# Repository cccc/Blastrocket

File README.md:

# Blastrocket - A C4 flavored Blinkenrocket

With KiCad made clone of the [https://github.com/blinkenrocket](blinkenrocket). Should be compatible with the original blinkenrocket, e.g. to use webbased [http://blinkenrocket.de/](programming tool) and the original build up manual.

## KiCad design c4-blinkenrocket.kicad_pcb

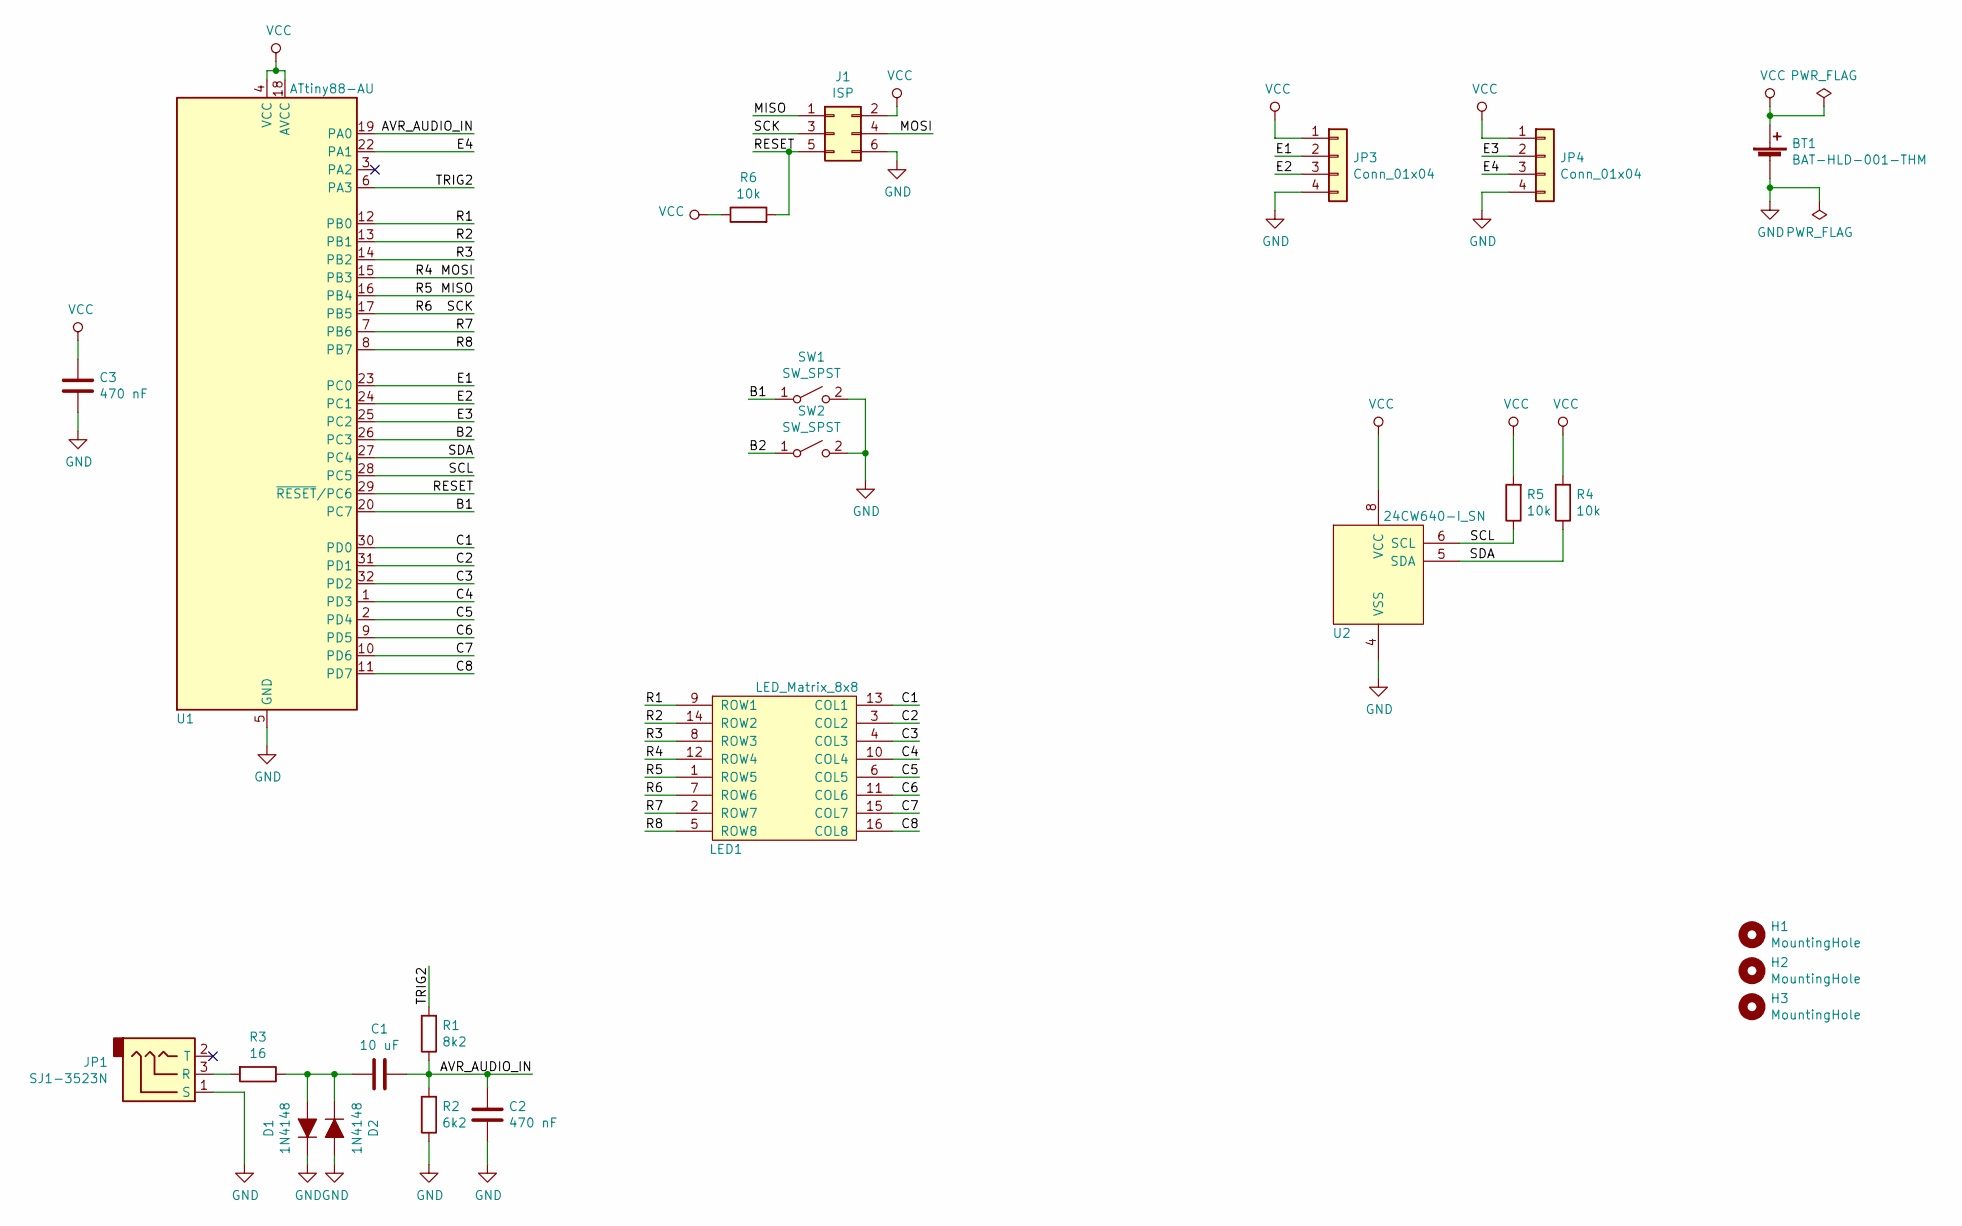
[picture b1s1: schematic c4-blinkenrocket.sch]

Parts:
BT1: BAT-HLD-001-THM; BAT_Linx_BAT-HLD-001-THM; Mfg Part Num BAT-HLD-001-THM; Digikey BAT-HLD-001-THM-ND
C1: 10 uF; C_1206_3216Metric_Pad1.42x1.75mm_HandSolder; Mfg Part Num CL31A106KAHNNNE; Digikey 1276-1075-1-ND
C2, C3: 470 nF; C_1206_3216Metric_Pad1.42x1.75mm_HandSolder; Mfg Part Num CL31B474KBHNNNE; Digikey 1276-1118-1-ND
D1, D2: 1N4148; D_SOD-123; Mfg Part Num 1N4148WQ-7-F; Digikey 1N4148WQ-7-FDICT-ND
H1, H2, H3: MountingHole; MountingHole_3.2mm_M3_Pad
J1: ISP; PinHeader_2x03_P2.54mm_Vertical
JP1: SJ1-3523N; Jack_3.5mm_CUI_SJ1-3523N_Horizontal; Mfg Part Num SJ1-3523N; Digikey CP1-3523N-ND
JP3, JP4: Conn_01x04; PinHeader_1x04_P2.54mm_Vertical
LED1: LED_Matrix_8x8; LED_KWM-30881XVB_8x8_3mm_3.2x3.2mm
R1: 8k2; R_1206_3216Metric_Pad1.42x1.75mm_HandSolder; Mfg Part Num RC1206JR-078K2L; Digikey 311-8.2KERCT-ND
R2: 6k2; R_1206_3216Metric_Pad1.42x1.75mm_HandSolder; Mfg Part Num RC1206JR-076K2L; Digikey 311-6.2KERCT-ND
R3: 16; R_1206_3216Metric_Pad1.42x1.75mm_HandSolder; Mfg Part Num RC1206FR-0716RL; Digikey 311-16.0FRCT-ND
R4, R5, R6: 10k; R_1206_3216Metric_Pad1.42x1.75mm_HandSolder; Mfg Part Num RC1206JR-0710KL; Digikey 311-10KERCT-ND
SW1, SW2: SW_SPST; SW_PUSH_6mm_H5mm; Mfg Part Num 1825910-7; Digikey 450-1804-ND
U1: ATtiny88-AU; TQFP-32_7x7mm_P0.8mm_Handsolder; Mfg Part Num ATTINY88-AU; Digikey ATTINY88-AU-ND
U2: 24CW640-I_SN; SOIC-8_4.9x3.9mm_P1.27mm_Handsolder; Mfg Part Num 24CW640-I/SN; Digikey 24CW640-I/SN-ND

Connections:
/AVR_AUDIO_IN: C1.1, C2.2, R1.1, R2.2, U1.19 (PA0)
/B1: SW1.1 (A), U1.20 (PC7)
/B2: SW2.1 (A), U1.26 (PC3)
/C1: LED1.13 (COL1), U1.30 (PD0)
/C2: LED1.3 (COL2), U1.31 (PD1)
/C3: LED1.4 (COL3), U1.32 (PD2)
/C4: LED1.10 (COL4), U1.1 (PD3)
/C5: LED1.6 (COL5), U1.2 (PD4)
/C6: LED1.11 (COL6), U1.9 (PD5)
/C7: LED1.15 (COL7), U1.10 (PD6)
/C8: LED1.16 (COL8), U1.11 (PD7)
/E1: JP3.2, U1.23 (PC0)
/E2: JP3.3, U1.24 (PC1)
/E3: JP4.2, U1.25 (PC2)
/E4: JP4.3, U1.22 (PA1)
/MISO: J1.1, LED1.1 (ROW5), U1.16 (PB4)
/MOSI: J1.4, LED1.12 (ROW4), U1.15 (PB3)
/R1: LED1.9 (ROW1), U1.12 (PB0)
/R2: LED1.14 (ROW2), U1.13 (PB1)
/R3: LED1.8 (ROW3), U1.14 (PB2)
/R6: J1.3, LED1.7 (ROW6), U1.17 (PB5)
/R7: LED1.2 (ROW7), U1.7 (PB6)
/R8: LED1.5 (ROW8), U1.8 (PB7)
/RESET: J1.5, R6.2, U1.29 (~RESET~/PC6)
/SCL: R5.1, U1.28 (PC5), U2.6 (SCL)
/SDA: R4.1, U1.27 (PC4), U2.5 (SDA)
/TRIG2: R1.2, U1.6 (PA3)
GND: BT1.2 (-), C2.1, C3.1, D1.1 (K), D2.2 (A), J1.6, JP1.1 (S), JP3.4, JP4.4, R2.1, SW1.2 (B), SW2.2 (B), U1.5 (GND), U1.21 (GND), U2.4 (VSS)
unnamed: C1.2, D1.2 (A), D2.1 (K), R3.1
unnamed: JP1.3 (R), R3.2
VCC: BT1.1 (+), C3.2, J1.2, JP3.1, JP4.1, R4.2, R5.2, R6.1, U1.4 (VCC), U1.18 (AVCC), U2.8 (VCC)

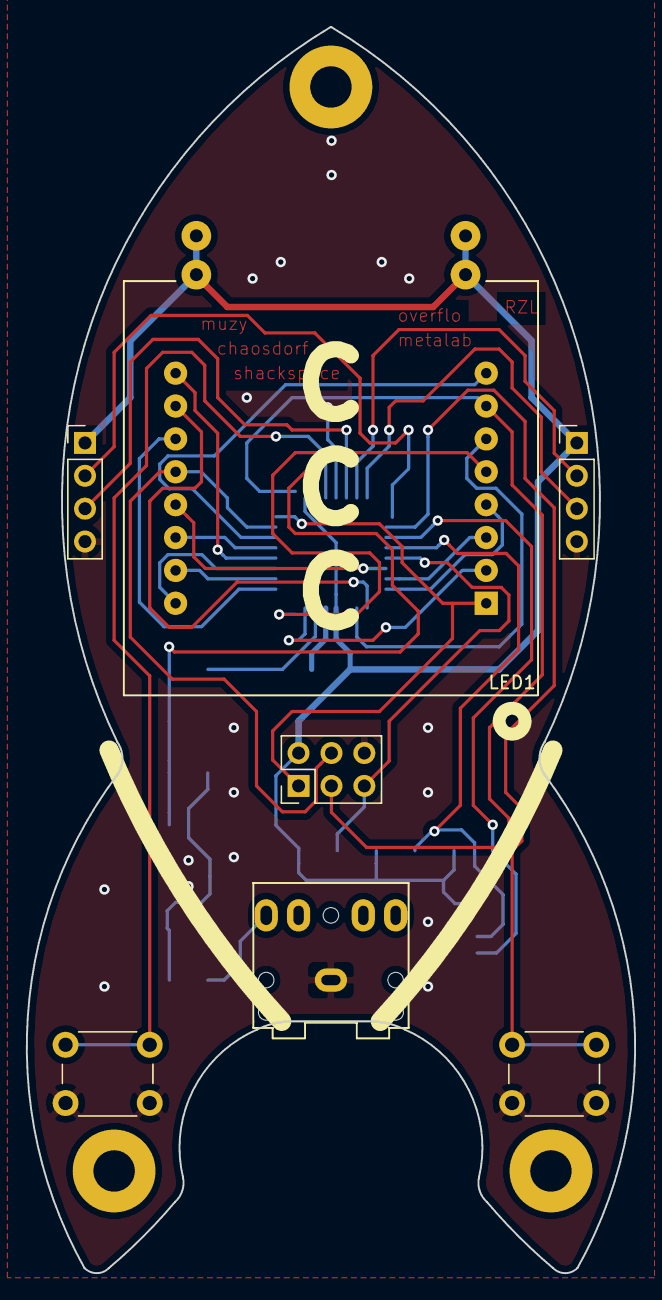
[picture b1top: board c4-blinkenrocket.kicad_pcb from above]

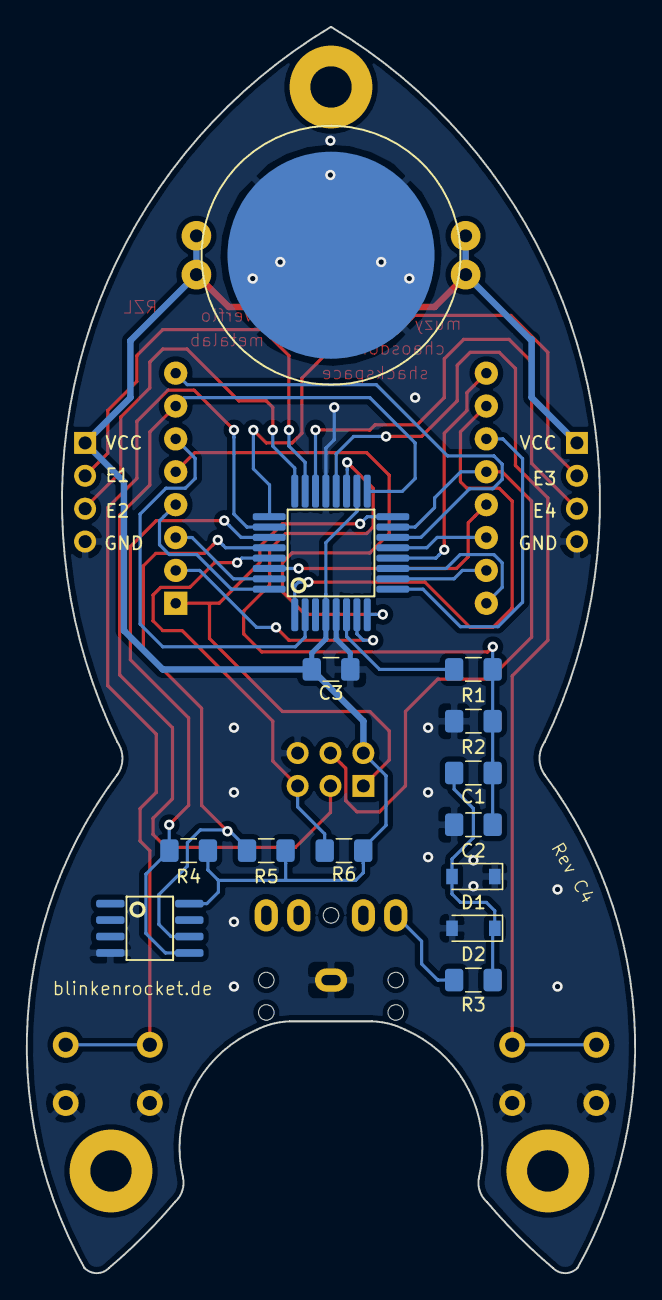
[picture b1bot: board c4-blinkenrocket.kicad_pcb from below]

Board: 2 copper layers, 47.0 x 96.3 mm, 24 parts (14 on the bottom side), 31 nets.

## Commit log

2019-05-01 Schematic: add uc and the modem. PCB: add the original border
2019-11-17 A first complete Version of the Blinkenrocket
2019-11-17 Swapped battery holder, made footprints easier to solder
2019-11-17 Fabrication data as ordered at the usual chinese pcb manufactures
